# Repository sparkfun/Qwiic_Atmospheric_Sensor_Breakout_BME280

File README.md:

SparkFun Atmospheric Sensor Breakout - BME280 (Qwiic)
========================================

[*SparkFun Atmospheric Sensor Breakout - BME280 (Qwiic) (SEN-15440)*](https://www.sparkfun.com/products/15440)

The SparkFun Atmospheric Sensor Breakout - BME280 (Qwiic) is perfect for sensing basic weather information. Using I2C, you can easily read data from the on-board BME280 sensor. This includes temperature, pressure, altitude and humidity.

Repository Contents
-------------------
* **/Hardware** - Eagle design files (.brd, .sch)
* **/Production** - Production panel files (.brd)

Documentation
--------------
* **[Arduino Library](https://github.com/sparkfun/SparkFun_BME280_Arduino_Library/)** - Arduino library for the BME280.
* **[Python Library](https://github.com/sparkfun/Qwiic_BME280_Py)** - Python library for the BME280.
* **[Fritzing Part](https://github.com/sparkfun/Fritzing_Parts/tree/main/products/15440_sfe_qwiic_atmospheric_sensor_BME280_pressure_humidity_temperature.fzpz)** - Fritzing part for the Qwiic BME280
* **[Hookup Guide](https://learn.sparkfun.com/tutorials/qwiic-atmospheric-sensor-bme280-hookup-guide)** - Basic hookup guide for the SparkFun Atmospheric Sensor Breakout - BME280 (Qwiic).
* **[Qwiic Ecosystem](https://www.sparkfun.com/qwiic)** - Qwiic enabled for fast prototyping!

Product Versions
----------------
* [SEN-13676](https://www.sparkfun.com/products/13676)- SparkFun Atmospheric Sensor Breakout - BME280
* [SEN-15440](https://www.sparkfun.com/products/15440)- SparkFun Atmospheric Sensor Breakout - BME280 (Qwiic).

License Information
-------------------

This product is _**open source**_! 

Please review the LICENSE.md file for license information. 

If you have any questions or concerns on licensing, please contact technical support on our [SparkFun forums](https://forum.sparkfun.com/viewforum.php?f=152).

Distributed as-is; no warranty is given.

- Your friends at SparkFun.

_<COLLABORATION CREDIT>_

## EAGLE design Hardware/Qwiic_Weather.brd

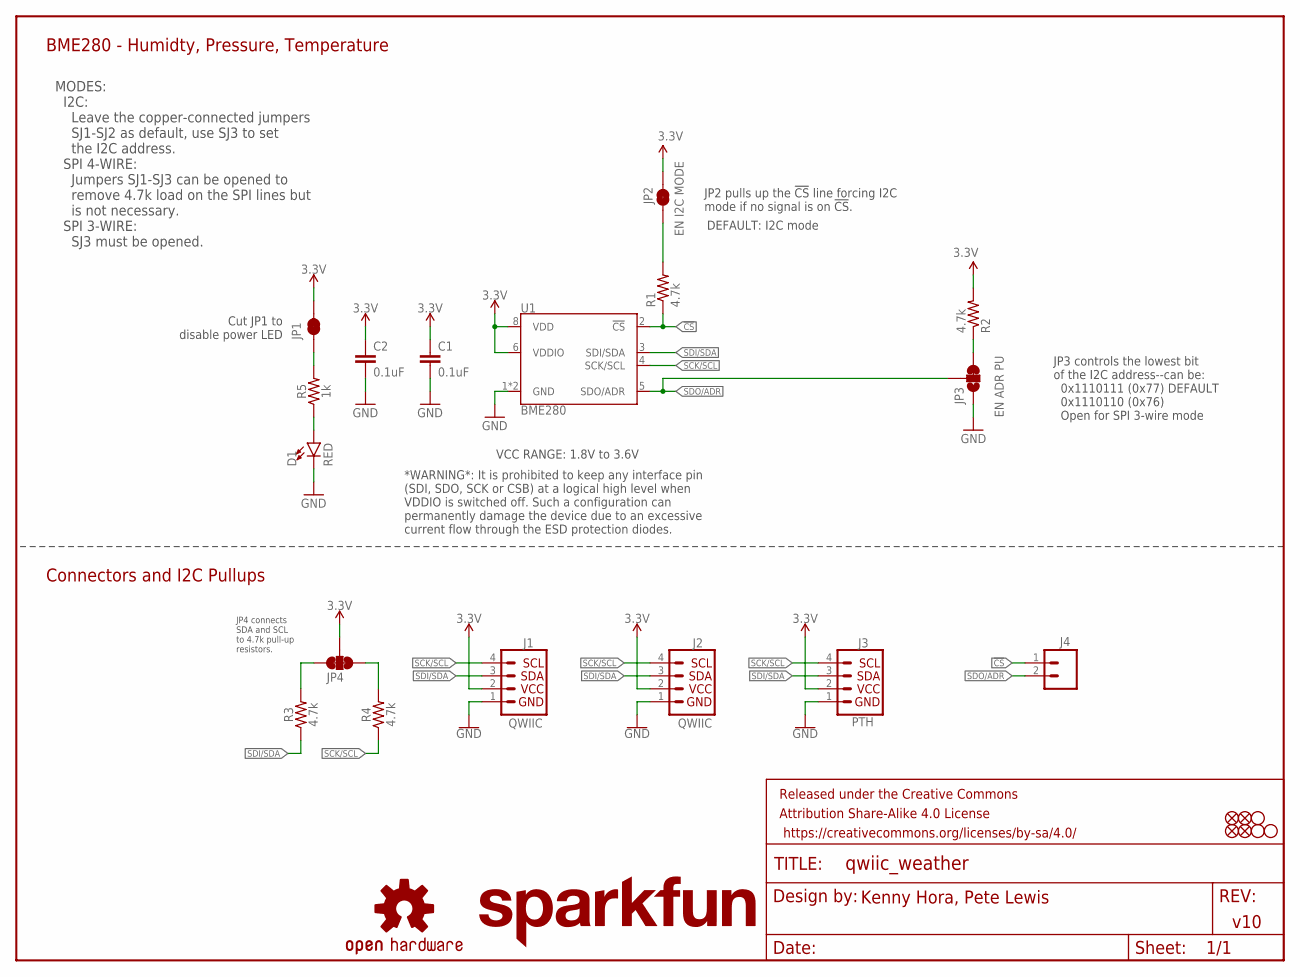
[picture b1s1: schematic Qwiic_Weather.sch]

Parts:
C1, C2: 0.1uF; 0603
D1: RED; LED-0603
FD1, FD2, FD3, FD4: FIDUCIAL1X2; FIDUCIAL-1X2
FRAME1: FRAME-LETTER; CREATIVE_COMMONS
H1, H2, H4: STAND-OFF
J1, J2: QWIIC; JST04_1MM_RA
J3: PTH; 1X04_NO_SILK
J4: CONN_021X02_NO_SILK; 1X02_NO_SILK
JP1: JUMPER-SMT_2_NC_TRACE_NO-SILK; SMT-JUMPER_2_NC_TRACE_NO-SILK
JP2: EN I2C MODE; PAD-JUMPER-2-NC_BY_TRACE_NO_SILK
JP3: EN ADR PU; SMT-JUMPER_3_1-NC_TRACE_NO-SILK
JP4: JUMPER-SMT_3_2-NC_TRACE_NO-SILK; SMT-JUMPER_3_2-NC_TRACE_NO-SILK
LOGO1: SFE_LOGO_NAME.1_INCH; SFE_LOGO_NAME_.1
LOGO4: OSHW-LOGOS; OSHW-LOGO-S
R1, R2, R3, R4: 4.7k; 0603
R5: 1k; 0603
U1: BME280; LGA-8-2.5X2.5

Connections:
3.3V: C1.1, C2.1, J1.2, J2.2, J3.2, JP1.2, JP2.2, JP4.2, R2.2, U1.6 (VDDIO), U1.8 (VDD)
!CS: J4.1, R1.1, U1.2 (!CS)
GND: C1.2, C2.2, D1.C, J1.1, J2.1, J3.1, JP3.1, U1.1 (GND), U1.7 (GND)
unnamed: JP3.3, R2.1
unnamed: D1.A, R5.1
unnamed: JP4.3, R3.2
unnamed: JP4.1, R4.2
unnamed: JP2.1, R1.2
unnamed: JP1.1, R5.2
SCK/SCL: J1.4, J2.4, J3.4, R4.1, U1.4 (SCK/SCL)
SDI/SDA: J1.3, J2.3, J3.3, R3.1, U1.3 (SDI/SDA)
SDO/ADR: J4.2, JP3.2, U1.5 (SDO/ADR)

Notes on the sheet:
JP4 connects SDA and SCL to 4.7k pull-up resistors.
v10
Kenny Hora, Pete Lewis
DEFAULT: I2C mode
BME280 - Humidty, Pressure, Temperature
JP2 pulls up the !CS! line forcing I2C mode if no signal is on !CS!.
JP3 controls the lowest bit of the I2C address--can be: 0x1110111 (0x77) DEFAULT 0x1110110 (0x76) Open for SPI 3-wire mode
MODES: I2C: Leave the copper-connected jumpers SJ1-SJ2 as default, use SJ3 to set the I2C address. SPI 4-WIRE: Jumpers SJ1-SJ3 can be opened to remove 4.7k load on the SPI lines but is not necessary. SPI 3-WIRE: SJ3 must be opened.
VCC RANGE: 1.8V to 3.6V
Connectors and I2C Pullups
Cut JP1 to disable power LED
*WARNING*: It is prohibited to keep any interface pin (SDI, SDO, SCK or CSB) at a logical high level when VDDIO is switched off. Such a configuration can permanently damage the device due to an excessive current flow through the ESD protection diodes.

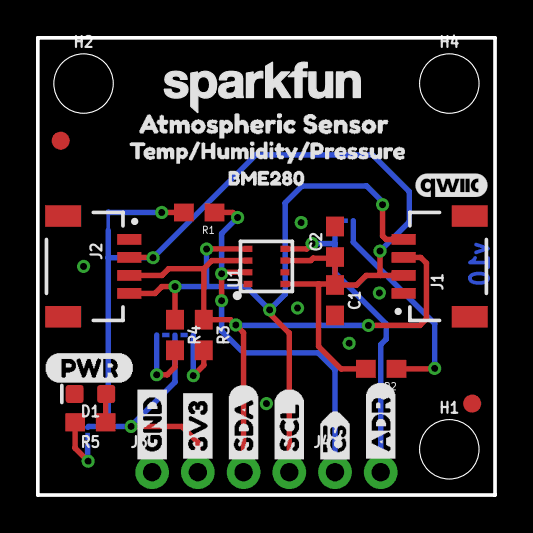
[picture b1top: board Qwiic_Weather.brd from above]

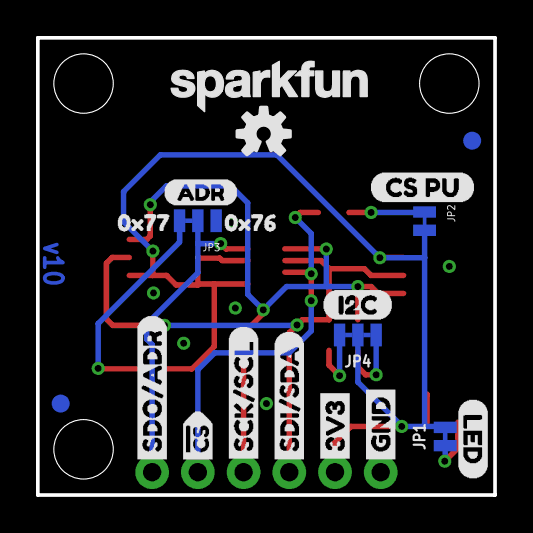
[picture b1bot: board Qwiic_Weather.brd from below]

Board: 2 copper layers, 25.4 x 25.4 mm, 51 parts (20 on the bottom side), 12 nets.

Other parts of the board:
LOGO3: SFE_LOGO_NAME.1_INCH; SFE_LOGO_NAME_.1@1
U$1: LED0
U$2, U$7: 3V34
U$3: ADR8
U$4, U$8: GND3
U$5: SDA5
U$6: SCL6
U$9: SDI#SDA11
U$10: SDO#ADR9
U$11: SCK#SCL10
U$13: PWR0
U$14, U$24: #CS0
U$15: BME2804
U$16: QWIIC_4MM
U$17: ATMOSPHERIC_SENSOR0
U$18: ADR2
U$19: 0X771
U$20: 0X760
U$21: CS_PU1
U$22: I2C0
U$23: TEMP#HUMIDITY#PRESSURE0

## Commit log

2019-06-17 switch to BME280
2019-06-18 added SPI cabability and some prelim buzzard label work
2019-06-19 Started routing board
    About 50% done. Added a power LED, adjusted silk.
2019-06-19 Finished Layout
    Finished Routing and Added pin and jumper labels.
2019-06-19 some small tweaks
    upped traces to 12 mil, nudged to avoid drc errors, added gnd via under connector.
2019-06-20 layout and library update work
    -updated 4.7K resistors to newest device (no silk under part).
    -removed some unncessary vis on 3.3V net, and rerouted.
    -nudges some traces and power LED for more efficient routing and better GND flow.
    -Moved Jumpers to no silk packages (for consistency)
2019-06-21 changes during checklist run 1
    -moved all text in sch to vector
    -removed unwanted value on jumper
    -4pin pth connector replaced with sparkfun library
    -vcc range added
    -dimension width to 8 mils
    -updated package on IC to fatten up silk width
2019-06-21 Changes during/post group design review
    -added power led disable jumper (and buzzard label and schematic text note).
    -switched CS to "pointer" flag label cuz it's an input.
    -added GND vias and nudges vias for better ground flow.
    -changed info line to short dash.
    -added text name for bottom half of schematic.
    -moved fids added third standoff.
2019-06-24 Post double-check changes
    -added IO warning in schematic
    -removed leftover CCS811 text object in tNames
    -designer name to vector
2019-07-30 updated hookup guide link
2019-08-21 Matching to product name
2019-08-21 Matching product name
2019-08-21 Update
    Relink photo and hookup guide, add python library, linked original breakout board
2019-08-21 Update contents section
2019-08-21 Create License

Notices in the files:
parts and their libraries:
SparkFun-Aesthetics: Licensing: Creative Commons ShareAlike 4.0 International - https://creativecommons.org/licenses/by-sa/4.0
SparkFun-Aesthetics: Released under the Creative Commons Attribution Share-Alike 4.0 License
SparkFun-Aesthetics: https://creativecommons.org/licenses/by-sa/4.0
